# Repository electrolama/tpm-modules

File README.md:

# tpm-modules

KiCAD (v5.99) designs for Infineon SLB9665 and SLB9670 based TPM modules.

There are two interfaces: SPI (SLB9670) and LPC (SLB9665). Pinouts for the modules vary a lot ([manufacturer specific?](https://superuser.com/a/1537838)) but given how simple the boards are adding new ones should be fairly straightforward. 

Modules in this repo:

**tpm-module-12pin-spi**

`Status:` Untested, parts ordered for prototypes

**tpm-module-14pin-lpc**

`Status:` Untested, please raise a PR if you build and test one.

**tpm-module-14pin-spi-asus**

`Status:` Untested, parts ordered for prototypes

If you do end up designing a new module, raise a PR so we can collect them all in one repo.

**UNTESTED DESIGNS - COMES WITH NO WARRANTIES OR PROMISES**

THIS MIGHT KILL YOUR COMPUTER AND SET YOUR HOUSE ON FIRE.

YOU HAVE BEEN WARNED.

**License:** CC0 "No Rights Reserved"

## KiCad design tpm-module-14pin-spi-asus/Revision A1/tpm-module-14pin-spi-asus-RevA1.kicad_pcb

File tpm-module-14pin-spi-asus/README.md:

Chip: [Infineon Optiga SLB 9670 TPM2.0](https://www.infineon.com/cms/en/product/security-smart-card-solutions/optiga-embedded-security-solutions/optiga-tpm/slb-9670vq2.0/)

Order codes:
SLB9670VQ20FW785XTMA1 (standard temp. range)
SLB9670XQ20FW785XUMA1 (extended temp. range)

Both options work. Package: PG-VQFN-32-13

Chip supply 1.8V or 3.3V, do not use with a 5V header (if that exists?)

Pinout taken from the user manual for ASUS PRIME B550-PLUS motherboard ([E16536_PRIME_B550-PLUS_UM_WEB_051420.pdf](https://dlcdnets.asus.com/pub/ASUS/mb/SocketAM4/PRIME_B550-PLUS/E16536_PRIME_B550-PLUS_UM_WEB_051420.pdf)). Pins highlighted in green are **educated guesses** for the ones used by the SPI-TPM module from ASUS.

**Important Note**: This module is meant to be installed in the *opposite* orientation as the ASUS module, as in the body of this module should face the CPU cooler, with the component side facing outwards. Unfortunately this module might clash with your cooler, this is untested at this moment. Module is designed this way because routing a super compact board would be very difficult and beyond my current abilities at this moment.

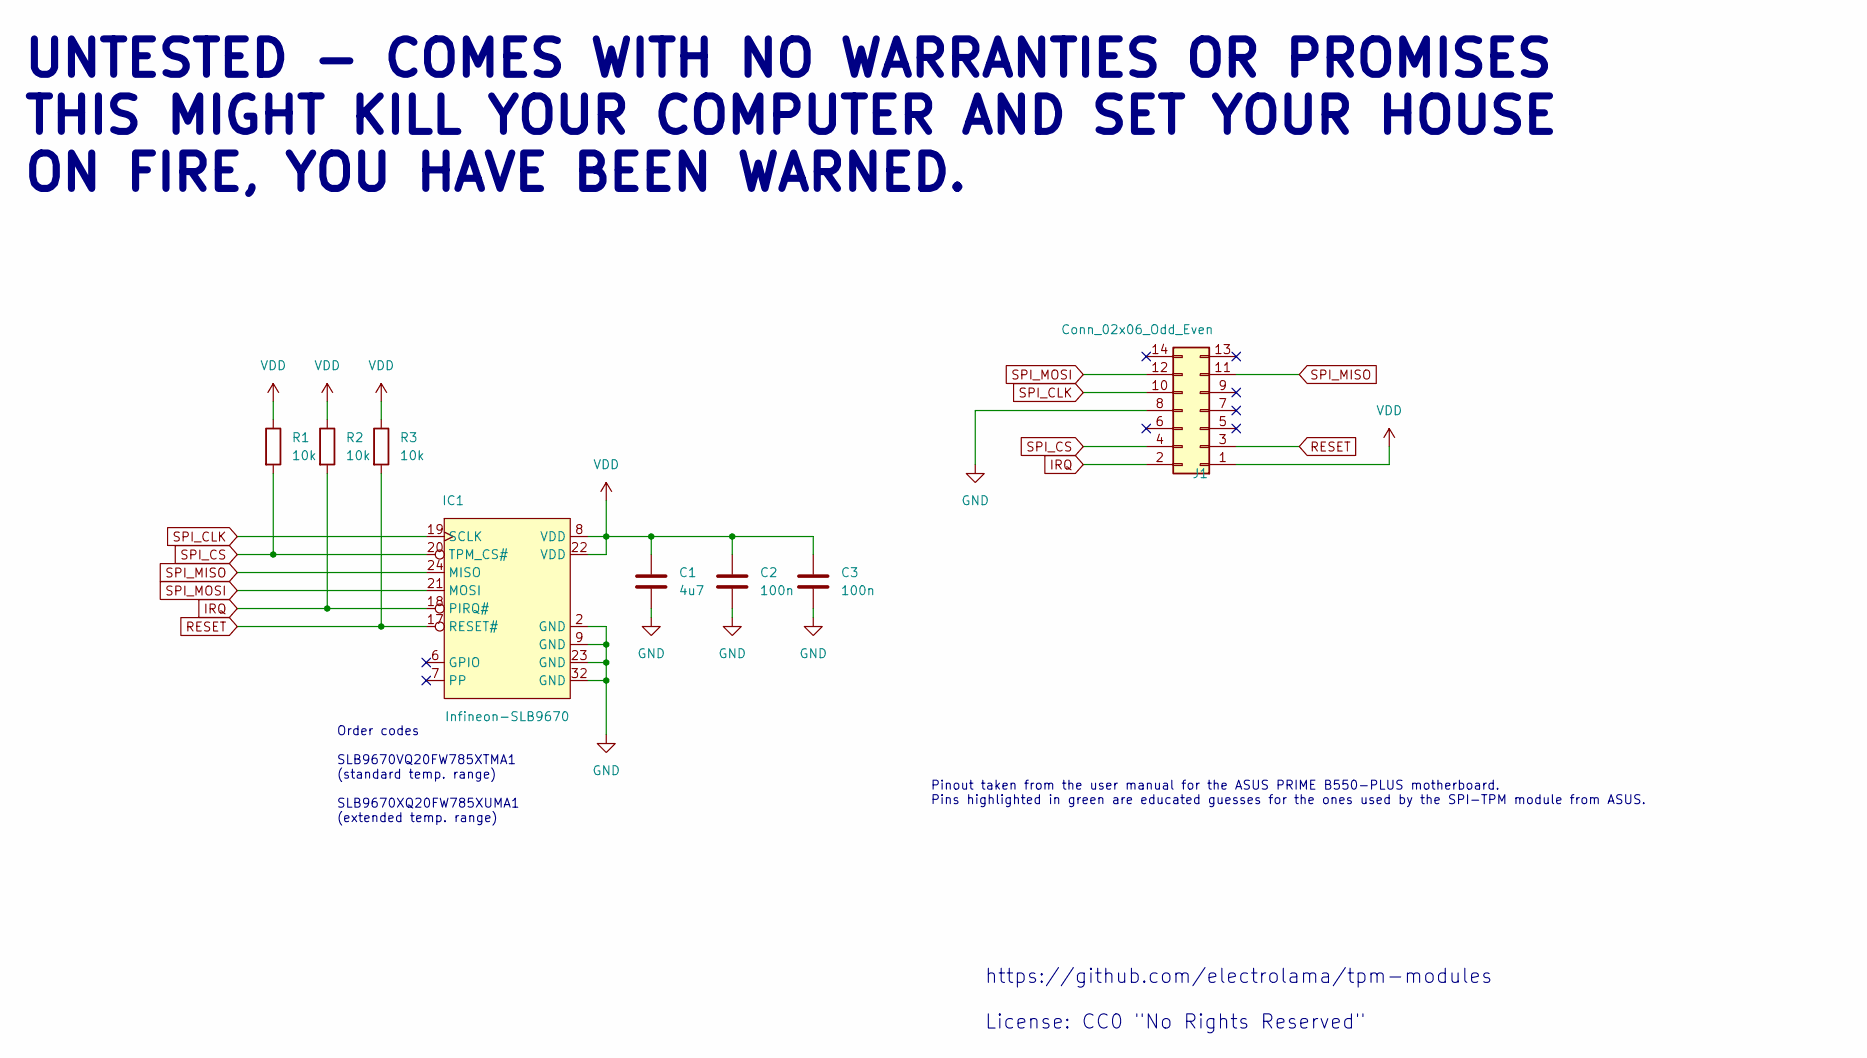
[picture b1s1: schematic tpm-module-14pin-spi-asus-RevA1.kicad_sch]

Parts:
C1: 4u7; C_0402_1005Metric
C2, C3: 100n; C_0402_1005Metric
IC1: Infineon-SLB9670; QFN-32-1EP_5x5mm_P0.5mm_EP3.1x3.1mm
J1: Conn_02x06_Odd_Even; PinSocket_2x07_P2.00mm_Vertical
R1, R2, R3: 10k; R_0402_1005Metric

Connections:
GND: C1.2, C2.2, C3.2, IC1.2 (GND), IC1.9 (GND), IC1.23 (GND), IC1.32 (GND), J1.8
IRQ: IC1.18 (PIRQ#), J1.2, R2.2
RESET: IC1.17 (RESET#), J1.3, R3.2
SPI_CLK: IC1.19 (SCLK), J1.10
SPI_CS: IC1.20 (TPM_CS#), J1.4, R1.2
SPI_MISO: IC1.24 (MISO), J1.11
SPI_MOSI: IC1.21 (MOSI), J1.12
VDD: C1.1, C2.1, C3.1, IC1.8 (VDD), IC1.22 (VDD), J1.1, R1.1, R2.1, R3.1

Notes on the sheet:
UNTESTED - COMES WITH NO WARRANTIES OR PROMISES THIS MIGHT KILL YOUR COMPUTER AND SET YOUR HOUSE ON FIRE, YOU HAVE BEEN WARNED.
Order codes SLB9670VQ20FW785XTMA1 (standard temp. range) SLB9670XQ20FW785XUMA1 (extended temp. range)
Pinout taken from the user manual for the ASUS PRIME B550-PLUS motherboard. Pins highlighted in green are educated guesses for the ones used by the SPI-TPM module from ASUS.
https://github.com/electrolama/tpm-modules License: CC0 "No Rights Reserved"

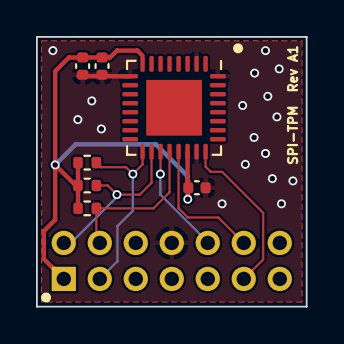
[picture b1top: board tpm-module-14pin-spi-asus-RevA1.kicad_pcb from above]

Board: 2 copper layers, 15.0 x 15.0 mm, 8 parts (1 on the bottom side), 8 nets.

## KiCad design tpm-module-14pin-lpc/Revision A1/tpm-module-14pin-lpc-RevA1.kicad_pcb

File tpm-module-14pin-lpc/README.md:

Chip: [Infineon Optiga SLB 9665 TPM2.0](https://www.infineon.com/cms/en/product/security-smart-card-solutions/optiga-embedded-security-solutions/optiga-tpm/slb-9665tt2.0/)

Order codes:

SLB9665VQ20FW563XUMA3 (standard temp. range)
SLB9665XQ20FW563XUMA2 (extended temp. range)

Both options work. Package: PG-VQFN-32-13

Chip supply 3.3V, do not use with a 5V header (if that exists?)

Pinout taken from

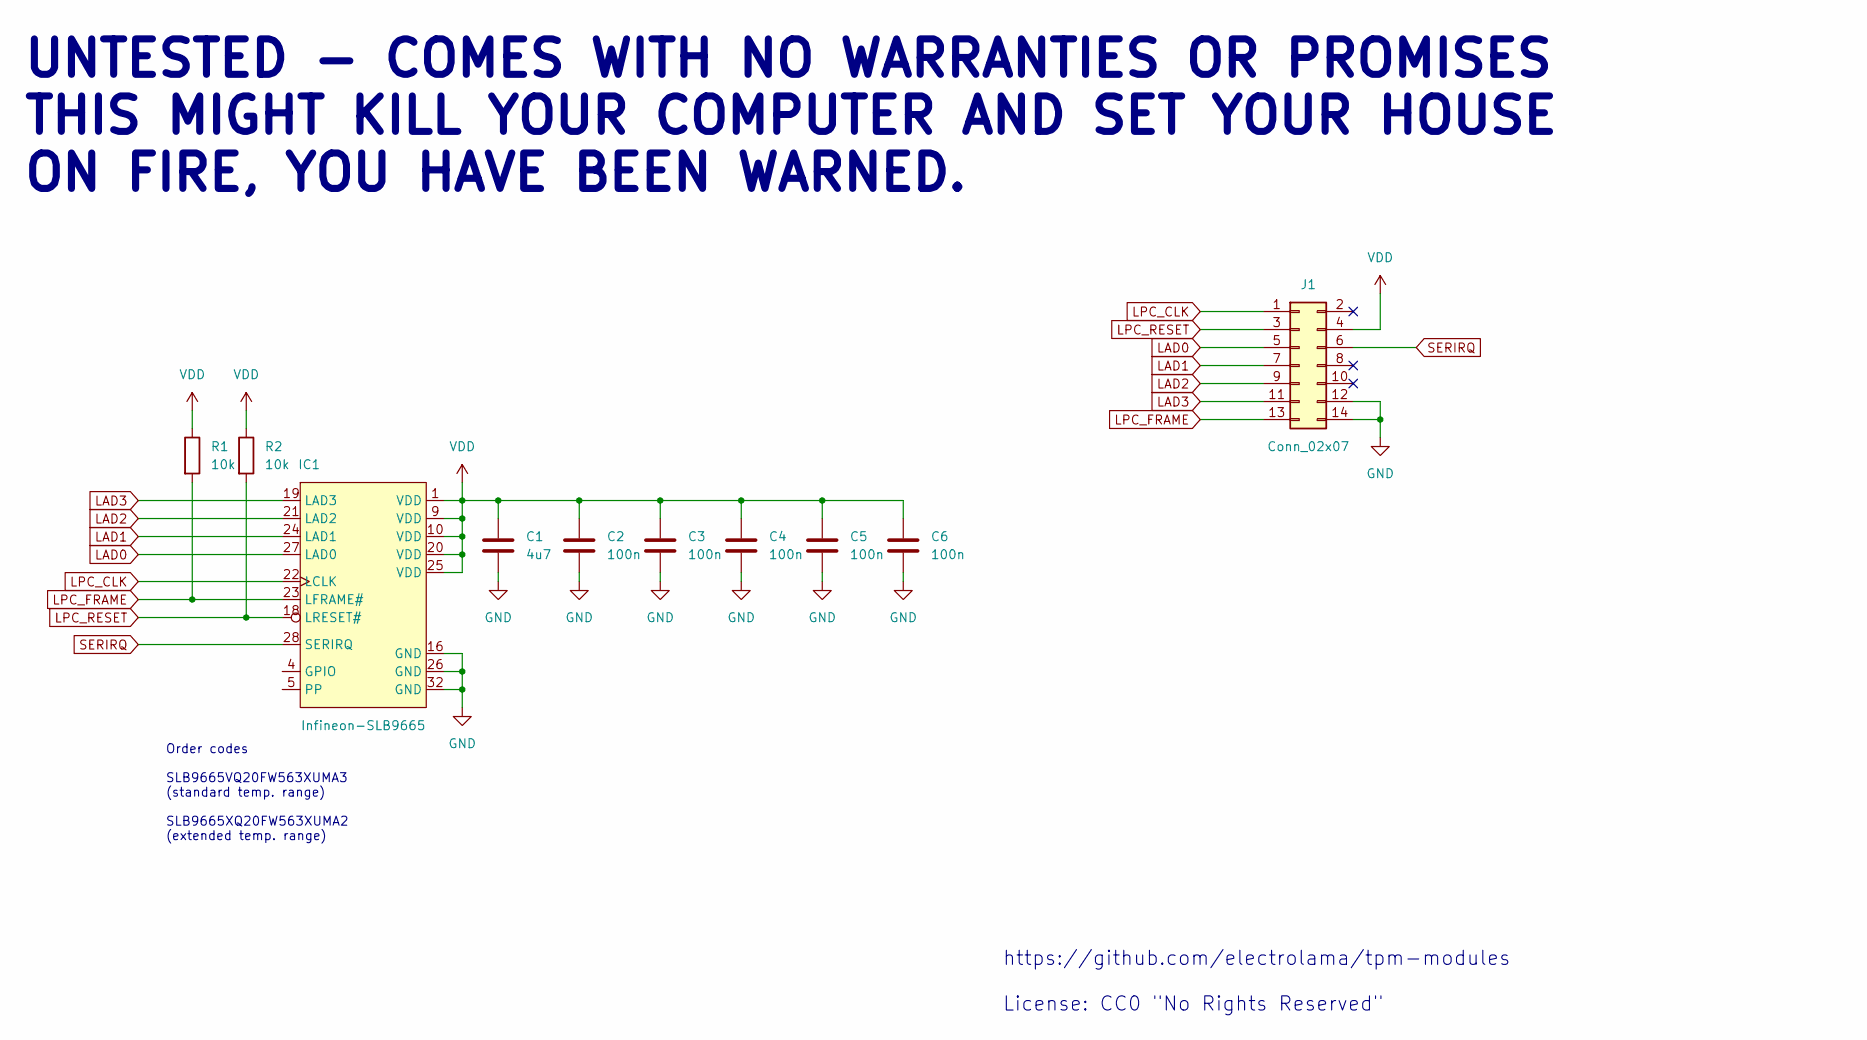
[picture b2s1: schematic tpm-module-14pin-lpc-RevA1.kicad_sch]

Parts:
C1: 4u7; C_0402_1005Metric
C2, C3, C4, C5, C6: 100n; C_0402_1005Metric
IC1: Infineon-SLB9665; QFN-32-1EP_5x5mm_P0.5mm_EP3.1x3.1mm
J1: Conn_02x07; PinSocket_2x07_P2.54mm_Horizontal
R1, R2: 10k; R_0402_1005Metric

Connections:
GND: C1.2, C2.2, C3.2, C4.2, C5.2, C6.2, IC1.16 (GND), IC1.26 (GND), IC1.32 (GND), J1.12, J1.14
LAD0: IC1.27 (LAD0), J1.5
LAD1: IC1.24 (LAD1), J1.7
LAD2: IC1.21 (LAD2), J1.9
LAD3: IC1.19 (LAD3), J1.11
LPC_CLK: IC1.22 (LCLK), J1.1
LPC_FRAME: IC1.23 (LFRAME#), J1.13, R1.2
LPC_RESET: IC1.18 (LRESET#), J1.3, R2.2
SERIRQ: IC1.28 (SERIRQ), J1.6
VDD: C1.1, C2.1, C3.1, C4.1, C5.1, C6.1, IC1.1 (VDD), IC1.9 (VDD), IC1.10 (VDD), IC1.20 (VDD), IC1.25 (VDD), J1.4, R1.1, R2.1

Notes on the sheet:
UNTESTED - COMES WITH NO WARRANTIES OR PROMISES THIS MIGHT KILL YOUR COMPUTER AND SET YOUR HOUSE ON FIRE, YOU HAVE BEEN WARNED.
Order codes SLB9665VQ20FW563XUMA3 (standard temp. range) SLB9665XQ20FW563XUMA2 (extended temp. range)
https://github.com/electrolama/tpm-modules License: CC0 "No Rights Reserved"

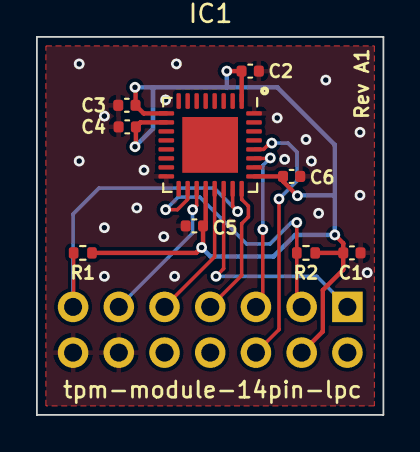
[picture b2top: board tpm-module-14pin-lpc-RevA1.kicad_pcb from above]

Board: 2 copper layers, 19.2 x 21.0 mm, 10 parts (1 on the bottom side), 10 nets.

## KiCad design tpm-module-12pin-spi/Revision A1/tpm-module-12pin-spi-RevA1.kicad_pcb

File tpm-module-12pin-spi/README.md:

Chip: [Infineon Optiga SLB 9670 TPM2.0](https://www.infineon.com/cms/en/product/security-smart-card-solutions/optiga-embedded-security-solutions/optiga-tpm/slb-9670vq2.0/)

Order codes:
SLB9670VQ20FW785XTMA1 (standard temp. range)
SLB9670XQ20FW785XUMA1 (extended temp. range)

Both options work. Package: PG-VQFN-32-13

Chip supply 1.8V or 3.3V, do not use with a 5V header (if that exists?)

Pinout taken from the user manual for MSI MAG B550M MORTAR WIFI/ MAG B550M MORTAR motherboard ([M7C94v1.2-EURO-1.pdf](https://www.msi.com/Motherboard/support/MAG-B550M-MORTAR#down-manual)).

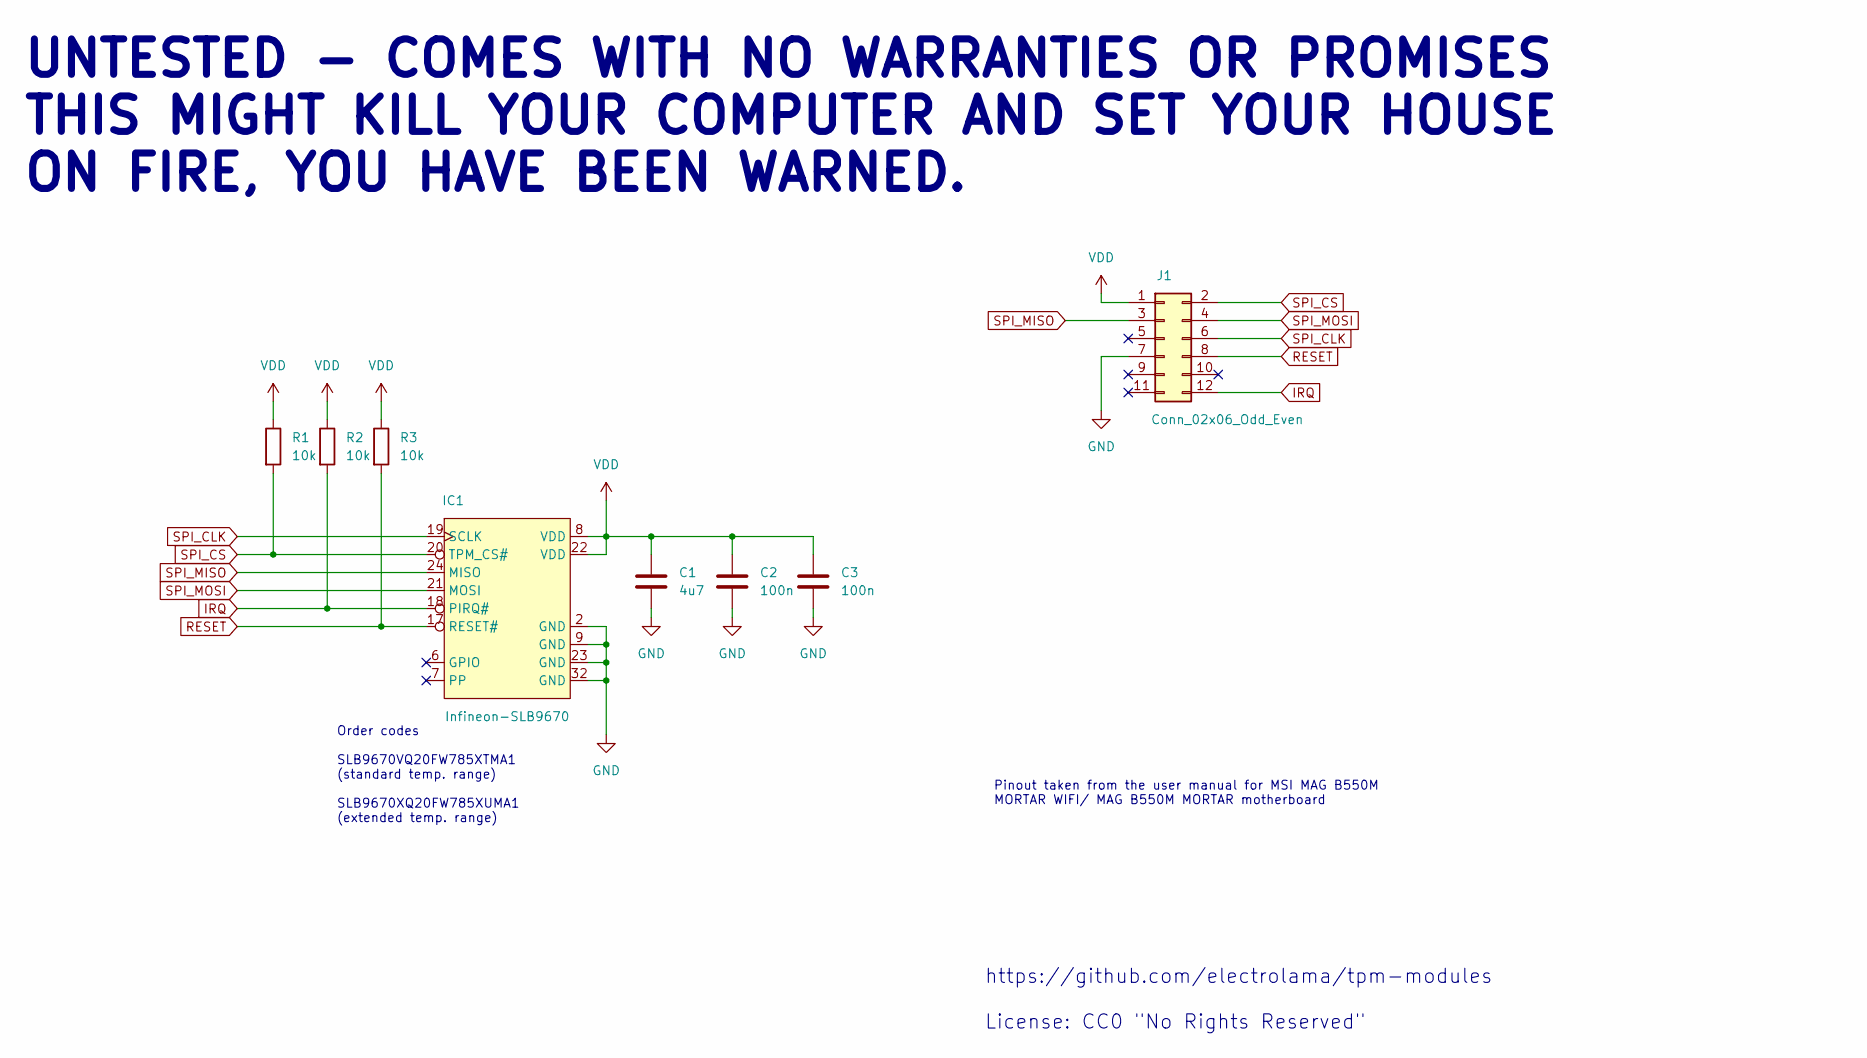
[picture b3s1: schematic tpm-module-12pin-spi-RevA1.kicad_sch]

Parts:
C1: 4u7; C_0402_1005Metric
C2, C3: 100n; C_0402_1005Metric
IC1: Infineon-SLB9670; QFN-32-1EP_5x5mm_P0.5mm_EP3.1x3.1mm
J1: Conn_02x06_Odd_Even; PinSocket_2x06_P2.54mm_Horizontal
R1, R2, R3: 10k; R_0402_1005Metric

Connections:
GND: C1.2, C2.2, C3.2, IC1.2 (GND), IC1.9 (GND), IC1.23 (GND), IC1.32 (GND), J1.7
IRQ: IC1.18 (PIRQ#), J1.12, R2.2
RESET: IC1.17 (RESET#), J1.8, R3.2
SPI_CLK: IC1.19 (SCLK), J1.6
SPI_CS: IC1.20 (TPM_CS#), J1.2, R1.2
SPI_MISO: IC1.24 (MISO), J1.3
SPI_MOSI: IC1.21 (MOSI), J1.4
VDD: C1.1, C2.1, C3.1, IC1.8 (VDD), IC1.22 (VDD), J1.1, R1.1, R2.1, R3.1

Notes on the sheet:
UNTESTED - COMES WITH NO WARRANTIES OR PROMISES THIS MIGHT KILL YOUR COMPUTER AND SET YOUR HOUSE ON FIRE, YOU HAVE BEEN WARNED.
Order codes SLB9670VQ20FW785XTMA1 (standard temp. range) SLB9670XQ20FW785XUMA1 (extended temp. range)
https://github.com/electrolama/tpm-modules License: CC0 "No Rights Reserved"
Pinout taken from the user manual for MSI MAG B550M MORTAR WIFI/ MAG B550M MORTAR motherboard

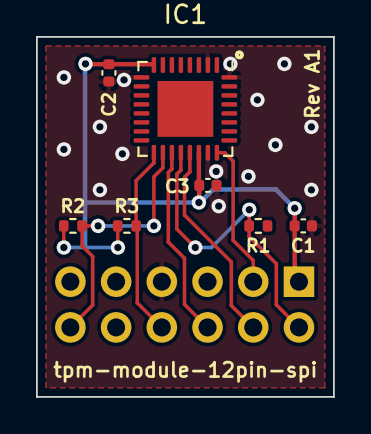
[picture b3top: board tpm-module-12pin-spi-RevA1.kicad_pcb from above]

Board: 2 copper layers, 16.5 x 20.0 mm, 8 parts (1 on the bottom side), 8 nets.

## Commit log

2021-06-26 add kicad symbols for SLB9665 and SLB9670
2021-06-26 initial commit for tpm-module-12pin-spi-RevA1
2021-06-26 initial commit for tpm-module-14pin-lpc-RevA1
2021-06-26 fix readme formatting
2021-08-29 add currently untested asus spi-tpm module
